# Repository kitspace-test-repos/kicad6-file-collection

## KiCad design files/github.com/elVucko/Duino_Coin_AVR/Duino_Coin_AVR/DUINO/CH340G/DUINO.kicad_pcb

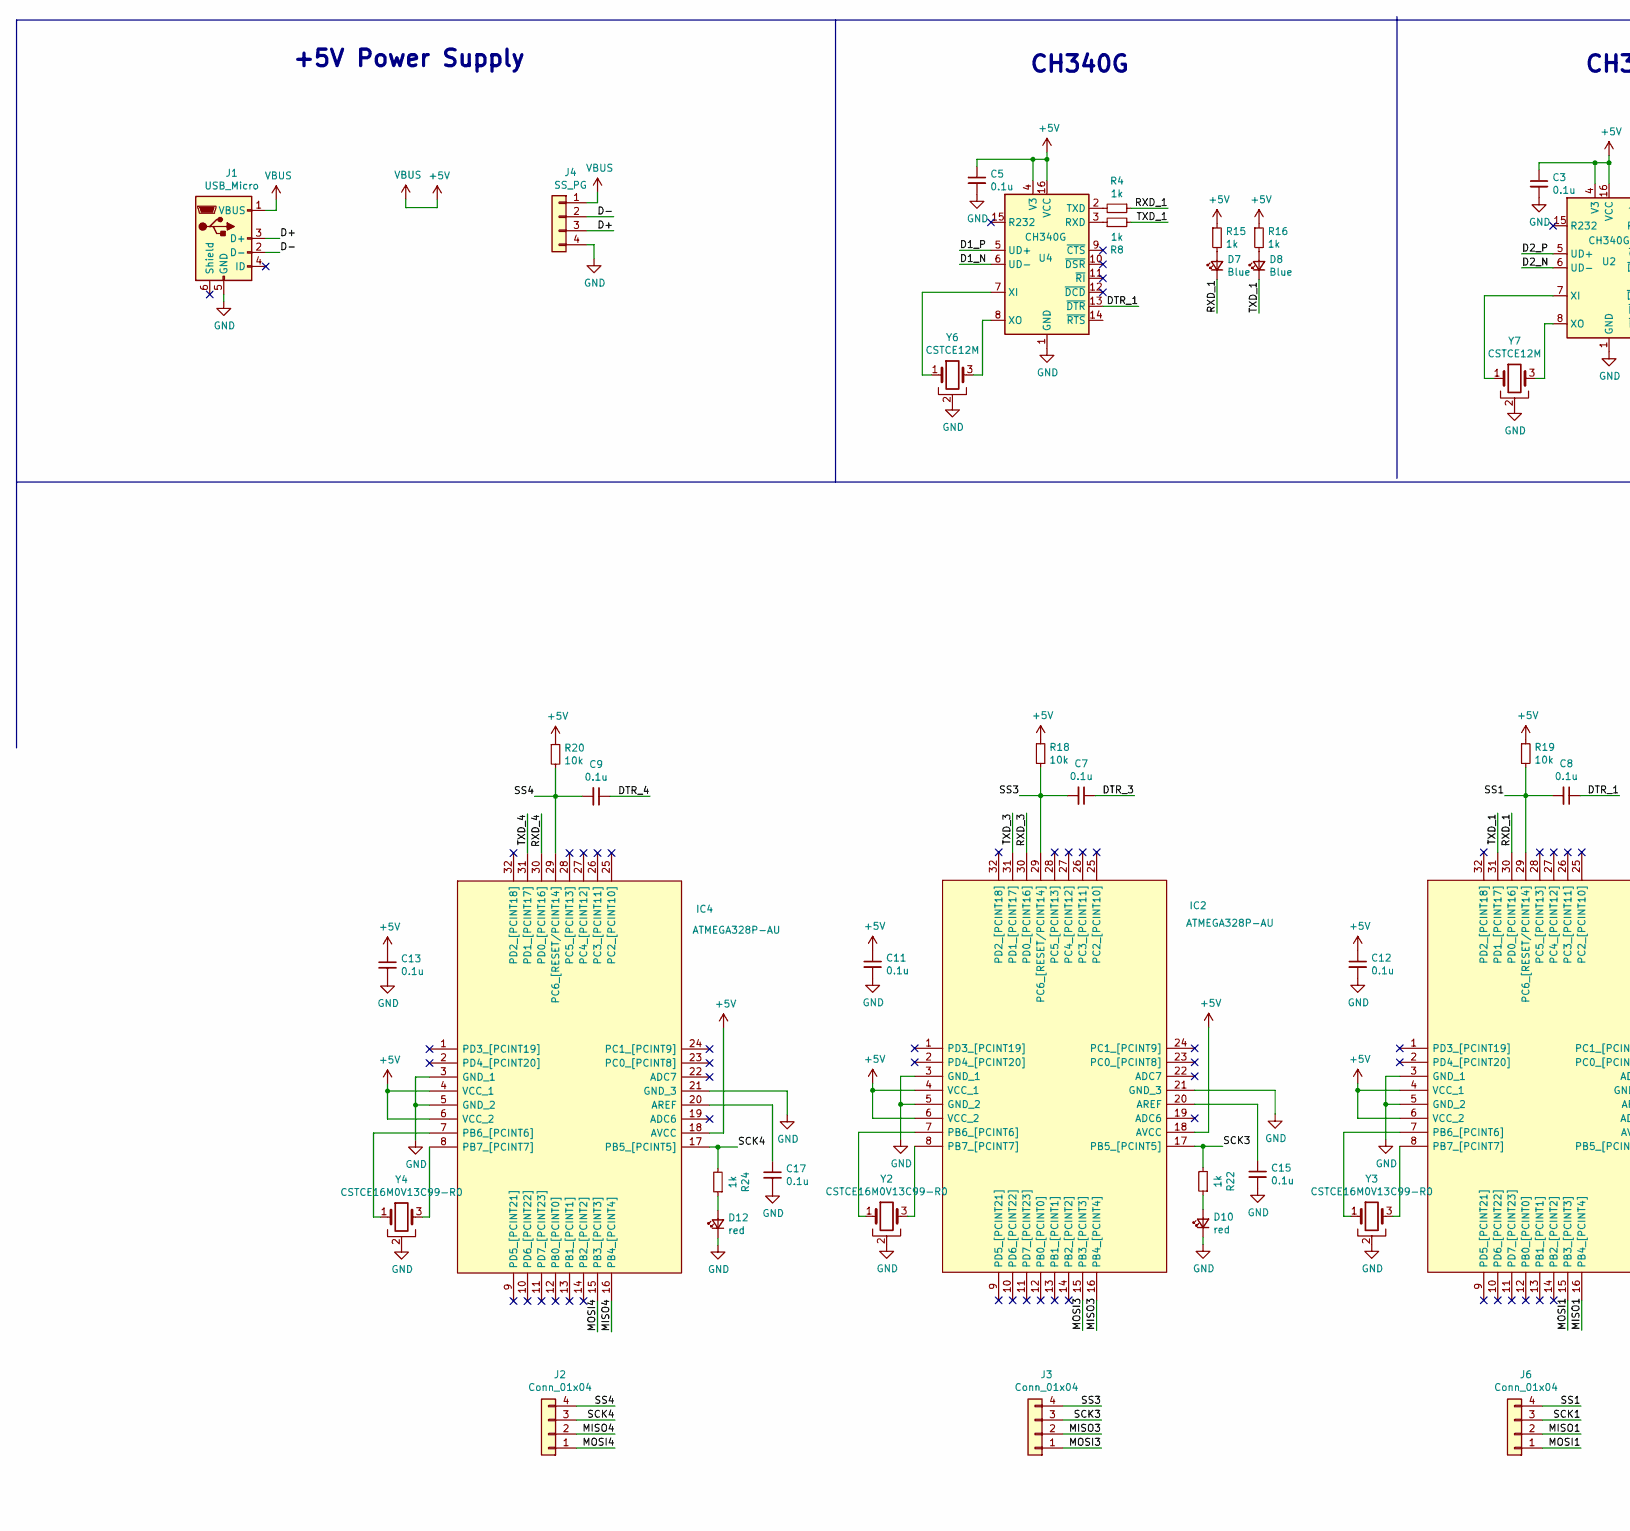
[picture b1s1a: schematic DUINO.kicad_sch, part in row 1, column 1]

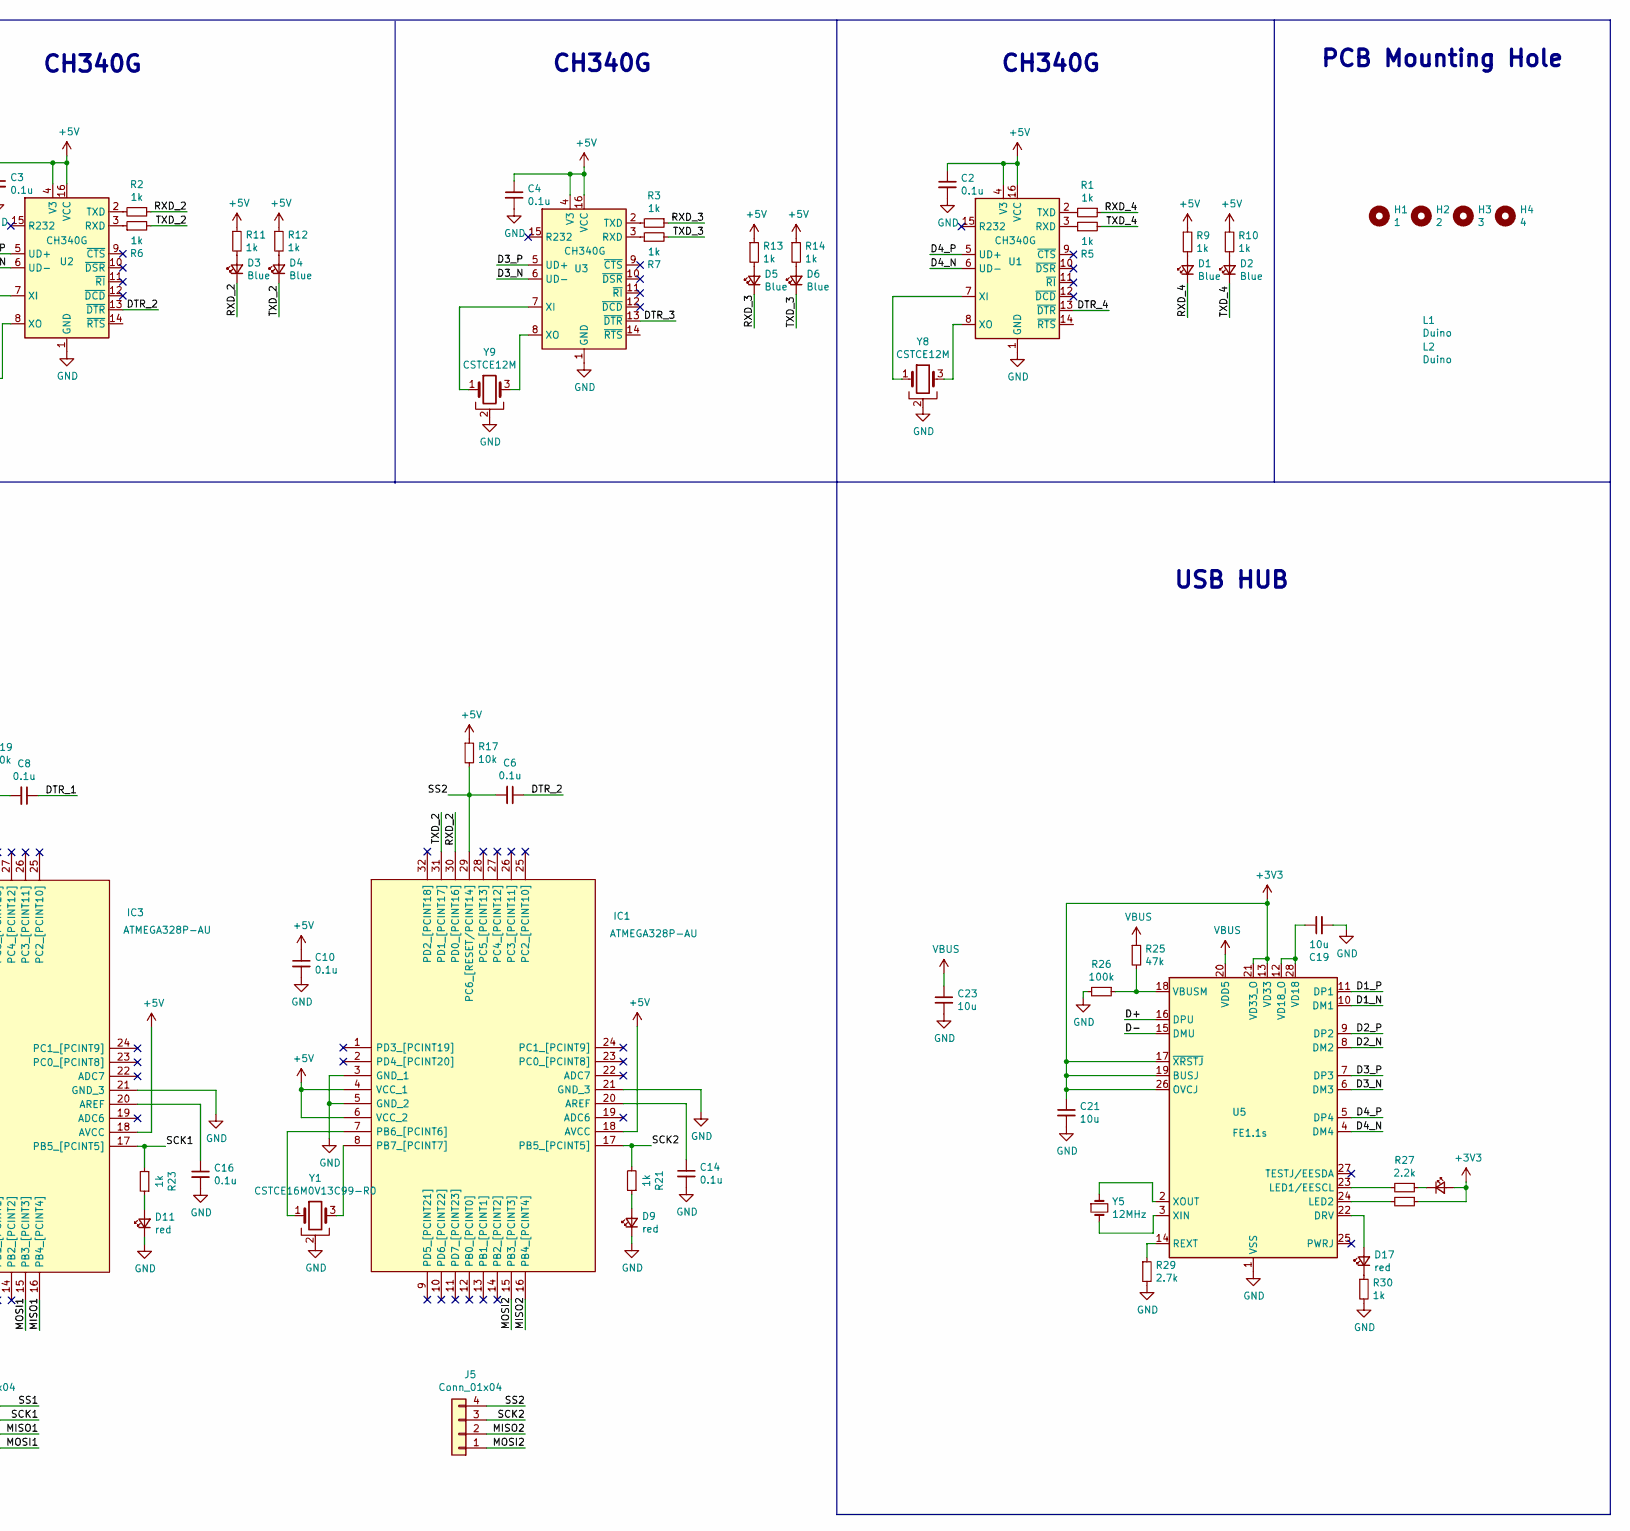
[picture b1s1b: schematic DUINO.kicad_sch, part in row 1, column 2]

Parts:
C2, C3, C4, C5, C6, C7, C8, C9, C10, C11, C12, C13, C14, C15, C16, C17: 0.1u; C_0805_2012Metric_Pad1.18x1.45mm_HandSolder
C19, C21, C23: 10u; C_0805_2012Metric_Pad1.18x1.45mm_HandSolder
D1, D2, D3, D4, D5, D6, D7, D8: Blue; LED_0603_1608Metric_Pad1.05x0.95mm_HandSolder
D9, D10, D11, D12, D17: red; LED_0603_1608Metric_Pad1.05x0.95mm_HandSolder
D13: 2; LED_0603_1608Metric_Pad1.05x0.95mm_HandSolder
H1: 1; MountingHole_3.2mm_M3
H2: 2; MountingHole_3.2mm_M3
H3: 3; MountingHole_3.2mm_M3
H4: 4; MountingHole_3.2mm_M3
IC1, IC2, IC3, IC4: ATMEGA328P-AU; QFP80P900X900X120-32N; Manufacturer_Part_Number ATMEGA328P-AU; Mouser Part Number 556-ATMEGA328P-AU
J1: USB_Micro; USB_Micro-B_Amphenol_10104110_Horizontal
J2, J3, J5, J6: Conn_01x04; PinHeader_1x04_P2.54mm_Vertical
J4: SS_PG; PinHeader_1x04_P2.54mm_Horizontal
L1, L2: Duino
R1, R2, R3, R4, R5, R6, R7, R8: 1k; R_0603_1608Metric_Pad0.98x0.95mm_HandSolder
R9, R10, R11, R12, R13, R14, R15, R16, R21, R22, R23, R24, R30: 1k; R_0805_2012Metric_Pad1.20x1.40mm_HandSolder
R17, R18, R19, R20: 10k; R_0805_2012Metric_Pad1.20x1.40mm_HandSolder
R25: 47k; R_0805_2012Metric_Pad1.20x1.40mm_HandSolder
R26: 100k; R_0805_2012Metric_Pad1.20x1.40mm_HandSolder
R27, R28: 2.2k; R_0805_2012Metric_Pad1.20x1.40mm_HandSolder
R29: 2.7k; R_0805_2012Metric_Pad1.20x1.40mm_HandSolder
U1, U2, U3, U4: CH340G; SOIC-16_3.9x9.9mm_P1.27mm
U5: FE1.1s; SSOP-28_3.9x9.9mm_P0.635mm
Y1, Y2, Y3, Y4: CSTCE16M0V13C99-R0; CSTCE16M0V13C99R0
Y5: 12MHz; Crystal_SMD_5032-2Pin_5.0x3.2mm
Y6, Y7, Y8, Y9: CSTCE12M; CSTCE16M0V13C99R0

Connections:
+3V3: C21.1, D13.2 (A), R28.1, U5.13 (VD33), U5.17 (~XRSTJ), U5.19 (BUSJ), U5.21 (VD33_O), U5.26 (OVCJ)
+5V: C2.1, C3.1, C4.1, C5.1, C10.1, C11.1, C12.1, C13.1, C23.1, IC1.4 (VCC_1), IC1.6 (VCC_2), IC1.18 (AVCC), IC2.4 (VCC_1), IC2.6 (VCC_2), IC2.18 (AVCC), IC3.4 (VCC_1), IC3.6 (VCC_2), IC3.18 (AVCC), IC4.4 (VCC_1), IC4.6 (VCC_2), IC4.18 (AVCC), J1.1 (VBUS), J4.1, R9.1, R10.1, R11.1, R12.1, R13.1, R14.1, R15.1, R16.1, R17.1, R18.1, R19.1, R20.1, R25.1, U1.4 (V3), U1.16 (VCC), U2.4 (V3), U2.16 (VCC), U3.4 (V3), U3.16 (VCC), U4.4 (V3), U4.16 (VCC), U5.20 (VDD5)
/D1_N: U4.6 (UD-), U5.10 (DM1)
/D1_P: U4.5 (UD+), U5.11 (DP1)
/D2_N: U2.6 (UD-), U5.8 (DM2)
/D2_P: U2.5 (UD+), U5.9 (DP2)
/D3_N: U3.6 (UD-), U5.6 (DM3)
/D3_P: U3.5 (UD+), U5.7 (DP3)
/D4_N: U1.6 (UD-), U5.4 (DM4)
/D4_P: U1.5 (UD+), U5.5 (DP4)
/D+: J1.3 (D+), J4.3, U5.16 (DPU)
/D-: J1.2 (D-), J4.2, U5.15 (DMU)
/DTR_1: C8.1, U4.13 (~DTR)
/DTR_2: C6.1, U2.13 (~DTR)
/DTR_3: C7.1, U3.13 (~DTR)
/DTR_4: C9.1, U1.13 (~DTR)
/MISO1: IC3.16 (PB4_[PCINT4]), J6.2
/MISO2: IC1.16 (PB4_[PCINT4]), J5.2
/MISO3: IC2.16 (PB4_[PCINT4]), J3.2
/MISO4: IC4.16 (PB4_[PCINT4]), J2.2
/MOSI1: IC3.15 (PB3_[PCINT3]), J6.1
/MOSI2: IC1.15 (PB3_[PCINT3]), J5.1
/MOSI3: IC2.15 (PB3_[PCINT3]), J3.1
/MOSI4: IC4.15 (PB3_[PCINT3]), J2.1
/RXD_1: D7.1 (K), IC3.30 (PD0_[PCINT16]), R4.1
/RXD_2: D3.1 (K), IC1.30 (PD0_[PCINT16]), R2.1
/RXD_3: D5.1 (K), IC2.30 (PD0_[PCINT16]), R3.1
/RXD_4: D1.1 (K), IC4.30 (PD0_[PCINT16]), R1.1
/SCK1: IC3.17 (PB5_[PCINT5]), J6.3, R23.2
/SCK2: IC1.17 (PB5_[PCINT5]), J5.3, R21.2
/SCK3: IC2.17 (PB5_[PCINT5]), J3.3, R22.2
/SCK4: IC4.17 (PB5_[PCINT5]), J2.3, R24.2
/SS1: C8.2, IC3.29 (PC6_[RESET/PCINT14]), J6.4, R19.2
/SS2: C6.2, IC1.29 (PC6_[RESET/PCINT14]), J5.4, R17.2
/SS3: C7.2, IC2.29 (PC6_[RESET/PCINT14]), J3.4, R18.2
/SS4: C9.2, IC4.29 (PC6_[RESET/PCINT14]), J2.4, R20.2
/TXD_1: D8.1 (K), IC3.31 (PD1_[PCINT17]), R8.2
/TXD_2: D4.1 (K), IC1.31 (PD1_[PCINT17]), R6.2
/TXD_3: D6.1 (K), IC2.31 (PD1_[PCINT17]), R7.2
/TXD_4: D2.1 (K), IC4.31 (PD1_[PCINT17]), R5.2
GND: C2.2, C3.2, C4.2, C5.2, C10.2, C11.2, C12.2, C13.2, C14.2, C15.2, C16.2, C17.2, C19.2, C21.2, C23.2, D9.1 (K), D10.1 (K), D11.1 (K), D12.1 (K), IC1.3 (GND_1), IC1.5 (GND_2), IC1.21 (GND_3), IC2.3 (GND_1), IC2.5 (GND_2), IC2.21 (GND_3), IC3.3 (GND_1), IC3.5 (GND_2), IC3.21 (GND_3), IC4.3 (GND_1), IC4.5 (GND_2), IC4.21 (GND_3), J1.5 (GND), J4.4, R26.2, R29.2, R30.2, U1.1 (GND), U2.1 (GND), U3.1 (GND), U4.1 (GND), U5.1 (VSS), Y1.2, Y2.2, Y3.2, Y4.2, Y6.2, Y7.2, Y8.2, Y9.2
unnamed: C14.1, IC1.20 (AREF)
unnamed: C15.1, IC2.20 (AREF)
unnamed: C16.1, IC3.20 (AREF)
unnamed: C17.1, IC4.20 (AREF)
unnamed: C19.1, U5.12 (VD18_O), U5.28 (VD18)
unnamed: D1.2 (A), R9.2
unnamed: D2.2 (A), R10.2
unnamed: D3.2 (A), R11.2
unnamed: D4.2 (A), R12.2
unnamed: D5.2 (A), R13.2
unnamed: D6.2 (A), R14.2
unnamed: D7.2 (A), R15.2
unnamed: D8.2 (A), R16.2
unnamed: D9.2 (A), R21.1
unnamed: D10.2 (A), R22.1
unnamed: D11.2 (A), R23.1
unnamed: D12.2 (A), R24.1
unnamed: D13.1 (K), R27.1
unnamed: D17.1 (K), R30.1
unnamed: D17.2 (A), U5.22 (DRV)
unnamed: IC1.7 (PB6_[PCINT6]), Y1.1
unnamed: IC1.8 (PB7_[PCINT7]), Y1.3
unnamed: IC2.7 (PB6_[PCINT6]), Y2.1
unnamed: IC2.8 (PB7_[PCINT7]), Y2.3
unnamed: IC3.7 (PB6_[PCINT6]), Y3.1
unnamed: IC3.8 (PB7_[PCINT7]), Y3.3
unnamed: IC4.7 (PB6_[PCINT6]), Y4.1
unnamed: IC4.8 (PB7_[PCINT7]), Y4.3
unnamed: R1.2, U1.2 (TXD)
unnamed: R2.2, U2.2 (TXD)
unnamed: R3.2, U3.2 (TXD)
unnamed: R4.2, U4.2 (TXD)
unnamed: R5.1, U1.3 (RXD)
unnamed: R6.1, U2.3 (RXD)
unnamed: R7.1, U3.3 (RXD)
unnamed: R8.1, U4.3 (RXD)
unnamed: R25.2, R26.1, U5.18 (VBUSM)
unnamed: R27.2, U5.23 (LED1/EESCL)
unnamed: R28.2, U5.24 (LED2)
unnamed: R29.1, U5.14 (REXT)
unnamed: U1.7 (XI), Y8.1
unnamed: U1.8 (XO), Y8.3
unnamed: U2.7 (XI), Y7.1
unnamed: U2.8 (XO), Y7.3
unnamed: U3.7 (XI), Y9.1
unnamed: U3.8 (XO), Y9.3
unnamed: U4.7 (XI), Y6.1
unnamed: U4.8 (XO), Y6.3
unnamed: U5.2 (XOUT), Y5.1
unnamed: U5.3 (XIN), Y5.2

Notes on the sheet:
CH340G
USB HUB
+5V Power Supply
PCB Mounting Hole

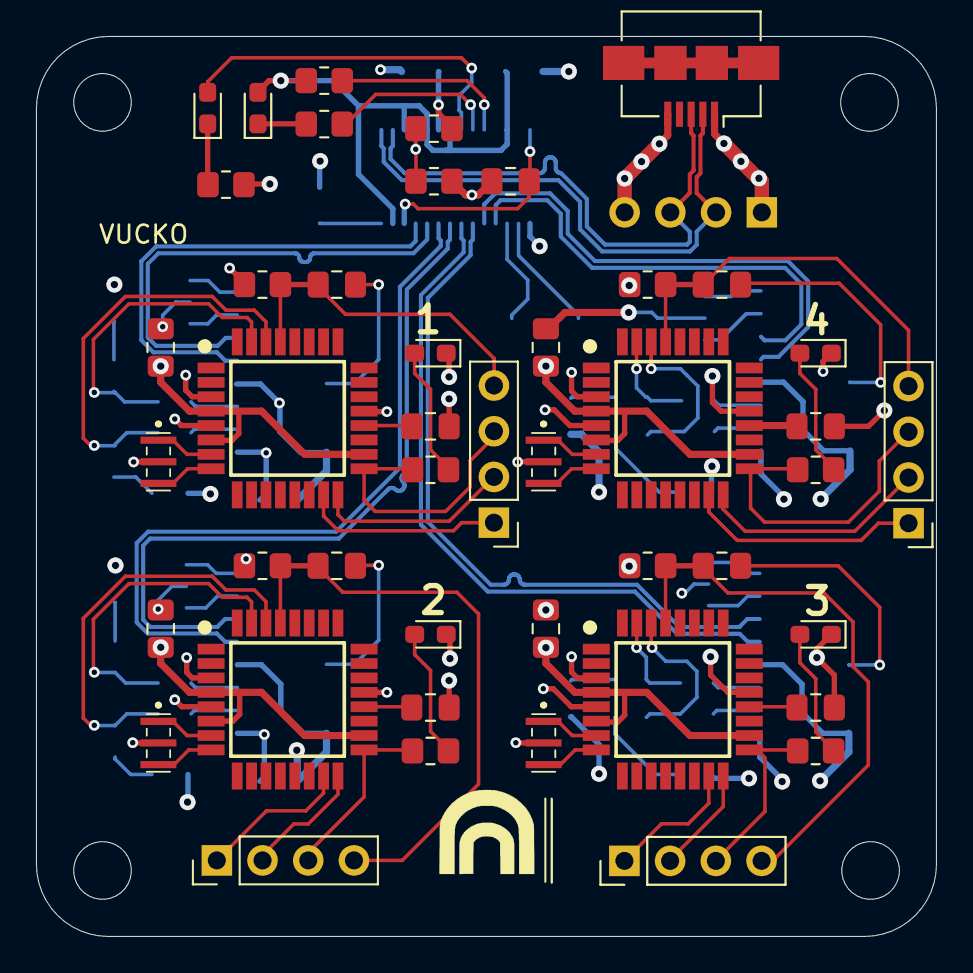
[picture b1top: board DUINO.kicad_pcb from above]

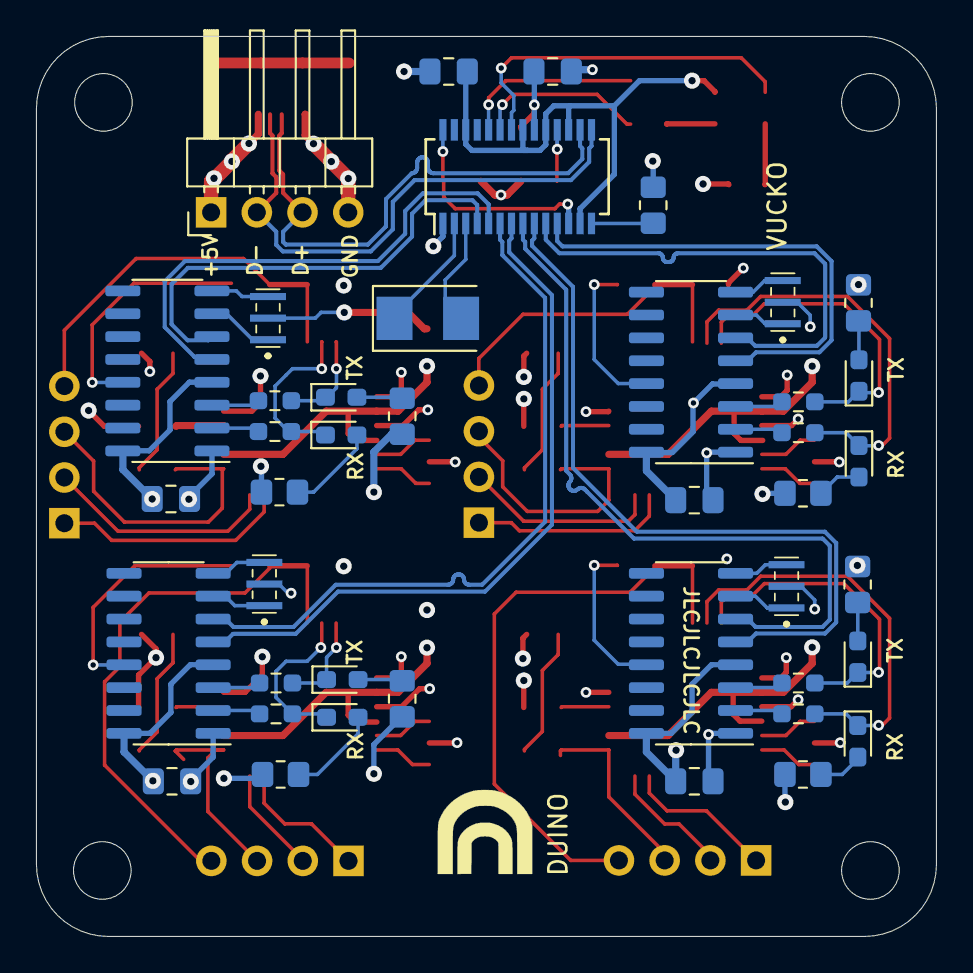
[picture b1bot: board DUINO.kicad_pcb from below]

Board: 4 copper layers, 50.0 x 50.0 mm, 93 parts (43 on the bottom side), 91 nets.

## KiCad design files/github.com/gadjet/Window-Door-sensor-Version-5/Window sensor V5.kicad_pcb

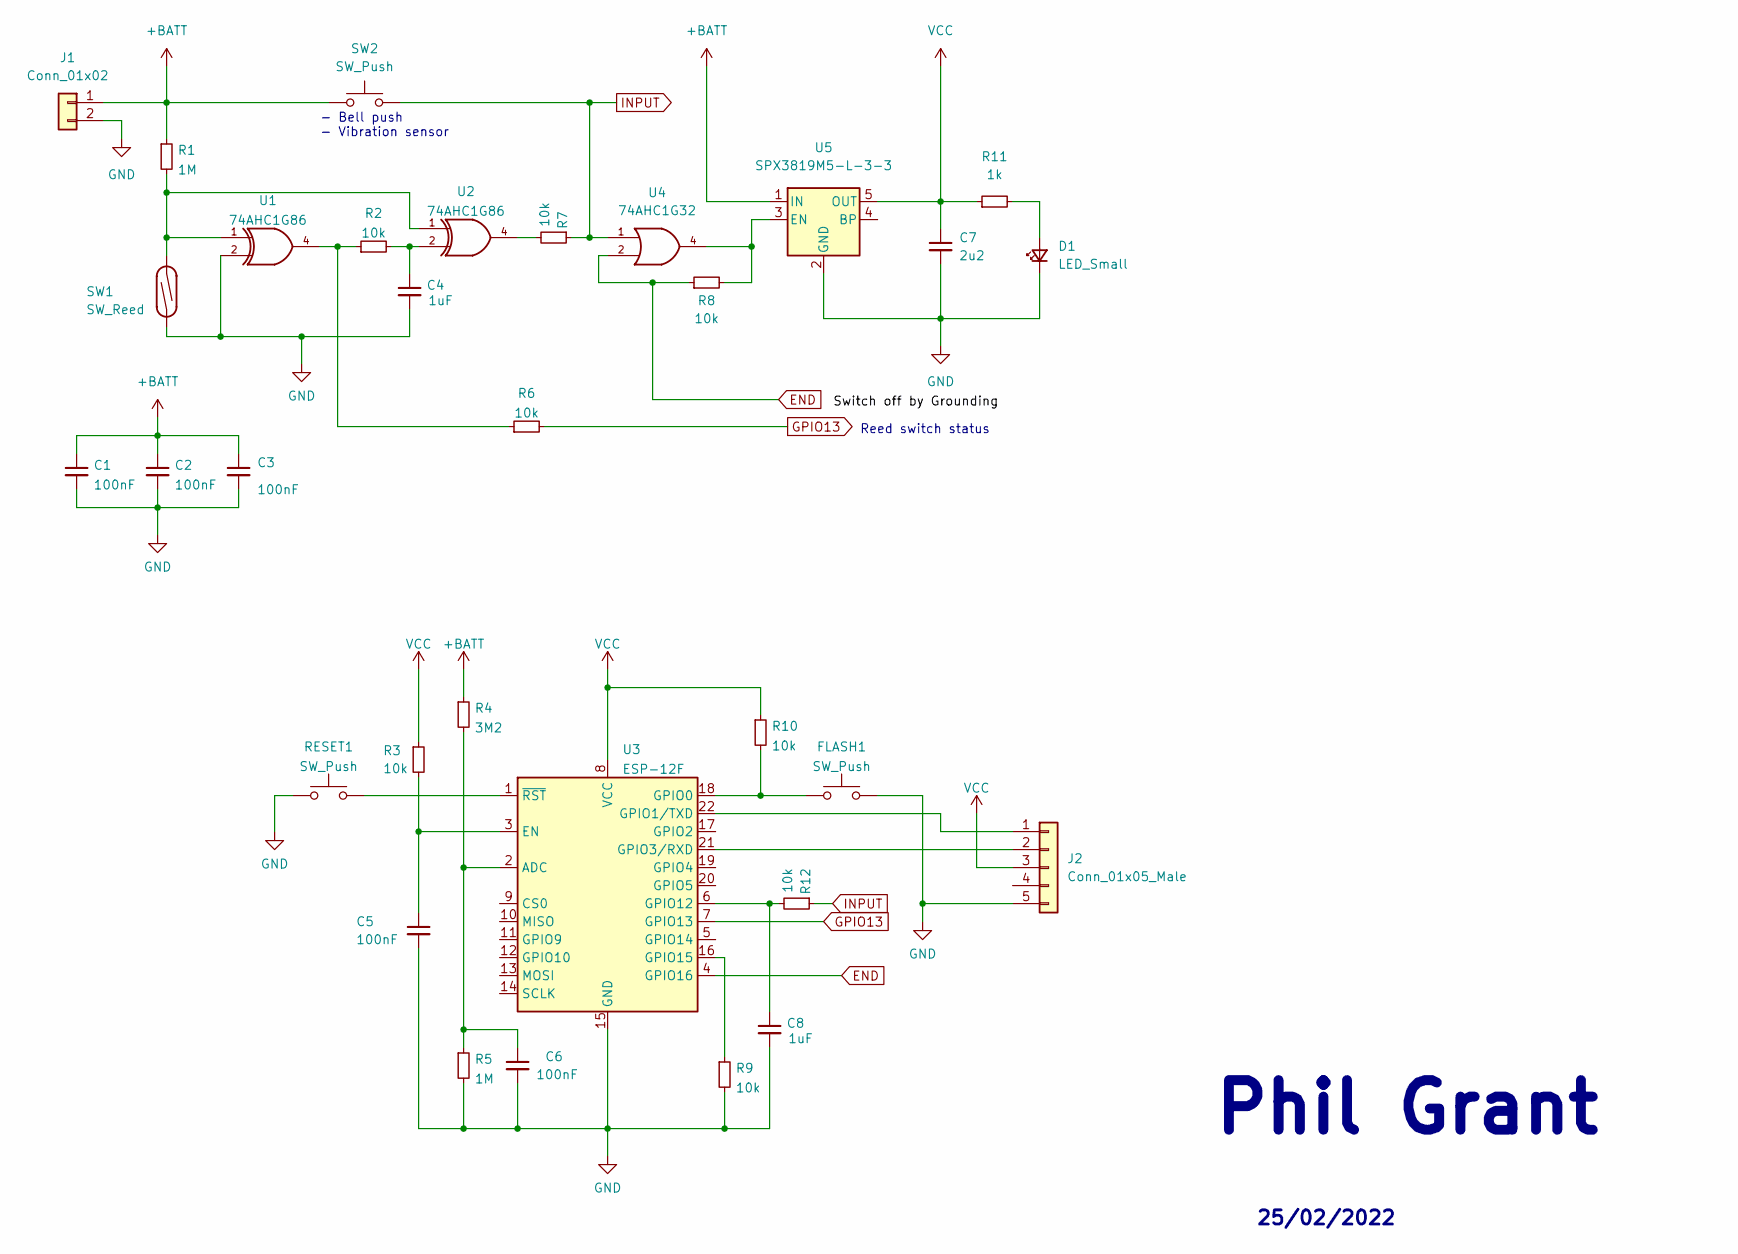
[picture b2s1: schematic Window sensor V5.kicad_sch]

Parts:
C1, C2, C3, C5, C6: 100nF; C_0603_1608Metric
C4, C8: 1uF; C_0603_1608Metric
C7: 2u2; C_0603_1608Metric
D1: LED_Small; LED_0805_2012Metric
FLASH1: SW_Push; SW_Push_SPST_NO_Alps_SKRK
J1: Conn_01x02; JST_PH_S2B-PH-K_1x02_P2.00mm_Horizontal
J2: Conn_01x05_Male; PinHeader_1x05_P2.54mm_Vertical
R1, R5: 1M; R_0603_1608Metric
R2, R3, R6, R7, R8, R9, R10, R12: 10k; R_0603_1608Metric
R4: 3M2; R_0603_1608Metric
R11: 1k; R_0603_1608Metric
RESET1: SW_Push; SW_Push_SPST_NO_Alps_SKRK
SW1: SW_Reed; SW_SPST_REED_CT10-XXXX-G2
SW2: SW_Push; SW_PUSH_6mm_H4.3mm
U1, U2: 74AHC1G86; SOT-23-5
U3: ESP-12F; ESP-12E
U4: 74AHC1G32; SOT-23-5
U5: SPX3819M5-L-3-3; SOT-23-5

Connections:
+BATT: C1.1, C2.1, C3.1, J1.1, R1.1, R4.1, SW2.1, U1.5 (+BATT), U2.5 (+BATT), U4.5 (+BATT), U5.1 (IN)
END: R8.1, U3.4 (GPIO16), U4.2
GND: C1.2, C2.2, C3.2, C4.2, C5.2, C6.2, C7.2, C8.2, D1.1 (K), FLASH1.2, J1.2, J2.5, R5.2, R9.2, RESET1.1, SW1.1, U1.2, U1.3 (GND), U2.3 (GND), U3.15 (GND), U4.3 (GND), U5.2 (GND); also elsewhere on the board
GPIO13: R6.2, U3.7 (GPIO13)
INPUT: R7.1, R12.1, SW2.2, U4.1
unnamed: C4.1, R2.2, U2.2
unnamed: C5.1, R3.2, U3.3 (EN)
unnamed: C6.1, R4.2, R5.1, U3.2 (ADC)
unnamed: C8.1, R12.2, U3.6 (GPIO12)
unnamed: D1.2 (A), R11.2
unnamed 10: FLASH1.1, R10.2, U3.18 (GPIO0); also elsewhere on the board
unnamed: J2.1, U3.22 (GPIO1/TXD)
unnamed: J2.2, U3.21 (GPIO3/RXD)
unnamed: R1.2, SW1.2, U1.1, U2.1
unnamed: R2.1, R6.1, U1.4
unnamed: R7.2, U2.4
unnamed: R8.2, U4.4, U5.3 (EN)
unnamed: R9.1, U3.16 (GPIO15)
unnamed 18: RESET1.2, U3.1 (~RST); also elsewhere on the board
VCC: C7.1, J2.3, R3.1, R10.1, R11.1, U3.8 (VCC), U5.5 (OUT)

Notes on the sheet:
- Bell push - Vibration sensor
25/02/2022
Reed switch status
Phil Grant

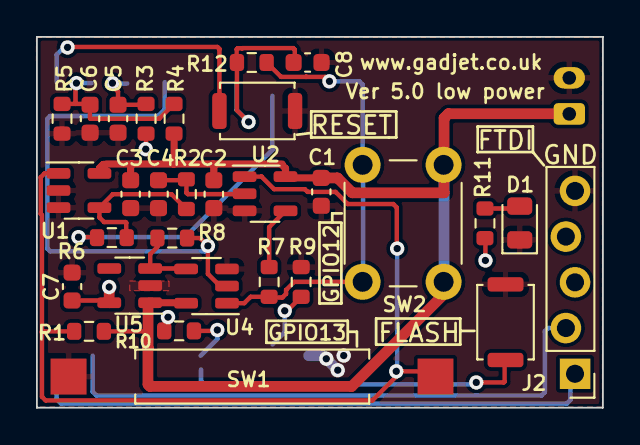
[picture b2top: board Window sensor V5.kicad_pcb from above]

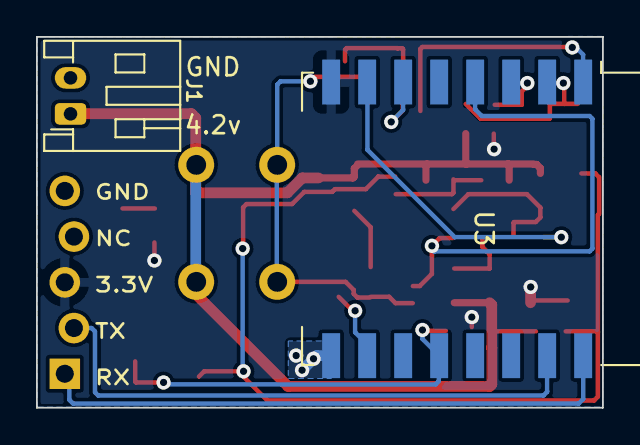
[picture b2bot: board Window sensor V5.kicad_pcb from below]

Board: 2 copper layers, 31.4 x 20.6 mm, 32 parts (2 on the bottom side), 20 nets.

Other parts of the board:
FLASH: SW_Push; SW_Push_SPST_NO_Alps_SKRK
RESET: SW_Push; SW_Push_SPST_NO_Alps_SKRK

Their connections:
GND: FLASH.2, RESET.1; also elsewhere on the board
unnamed 10: FLASH.1; also elsewhere on the board
unnamed 18: RESET.2; also elsewhere on the board

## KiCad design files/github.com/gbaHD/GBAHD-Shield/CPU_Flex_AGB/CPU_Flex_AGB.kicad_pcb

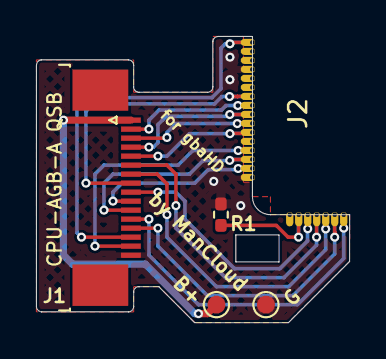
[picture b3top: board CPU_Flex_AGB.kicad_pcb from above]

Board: 2 copper layers, 17.4 x 15.9 mm, 5 parts (0 on the bottom side), 17 nets.

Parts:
B+: BAT+; TestPoint_Pad_D1.0mm
G: GND; TestPoint_Pad_D1.0mm
J1: Conn_01x16; TE_1-1734839-6_1x16-1MP_P0.5mm_Horizontal
J2: CPU_AGB_A_Interface; CPU_AGB_A_INTERFACE
R1: 100k; R_0402_1005Metric_Pad0.72x0.64mm_HandSolder

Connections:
GND: G.1, J1.16, J2.116 (GND), J2.128 (GND), R1.1
unnamed: J1.2, J2.120 (TP6)
unnamed: J1.3, J2.122 (TP7)
unnamed: J1.4, J2.121 (TP5)
unnamed: J1.5, J2.123 (TP4)
unnamed: J1.6, J2.4 (TP0)
unnamed: J1.7, J2.5 (TP1)
unnamed: J1.8, J2.119 (TP9)
unnamed: J1.9, J2.3 (TP8)
unnamed: J1.10, J2.127 (TP3)
unnamed: J1.11, J2.126 (TP2)
unnamed: J1.12, J2.7 (S02)
unnamed: J1.13, J2.6 (S01)
unnamed: J1.14, J2.113 (CK1)
unnamed: J1.15, J2.125 (RESET)
unnamed: J2.2 (IN35), R1.2
VCC: B+.1, J1.1

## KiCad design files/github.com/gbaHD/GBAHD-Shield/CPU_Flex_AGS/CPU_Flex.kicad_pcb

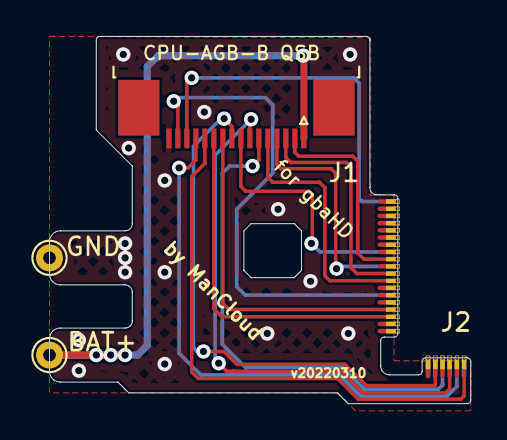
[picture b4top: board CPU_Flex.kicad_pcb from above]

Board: 2 copper layers, 23.4 x 20.4 mm, 4 parts (0 on the bottom side), 16 nets.

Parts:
BAT+: Conn_01x01; TestPoint_THTPad_D1.5mm_Drill0.7mm
GND: Conn_01x01; TestPoint_THTPad_D1.5mm_Drill0.7mm
J1: Conn_01x16; TE_1-1734839-6_1x16-1MP_P0.5mm_Horizontal
J2: CPU AGB B Interface; CPU_AGB_B_Interface

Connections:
/GBA_A: J1.6, J2.3 (TP0)
/GBA_AUD_L: J1.12, J2.6 (S02)
/GBA_AUD_R: J1.13, J2.5 (S01)
/GBA_B: J1.7, J2.4 (TP1)
/GBA_CLK: J1.14, J2.138 (CK1)
/GBA_DOWN: J1.3, J2.148 (TP7)
/GBA_L: J1.8, J2.145 (TP9)
/GBA_LEFT: J1.4, J2.147 (TP5)
/GBA_R: J1.9, J2.2 (TP8)
/GBA_RESET: J1.15, J2.151 (RESET)
/GBA_RIGHT: J1.5, J2.149 (TP4)
/GBA_SELECT: J1.11, J2.154 (TP2)
/GBA_START: J1.10, J2.153 (TP3)
/GBA_UP: J1.2, J2.146 (TP6)
GND: GND.1, J1.16
VCC: BAT+.1, J1.1

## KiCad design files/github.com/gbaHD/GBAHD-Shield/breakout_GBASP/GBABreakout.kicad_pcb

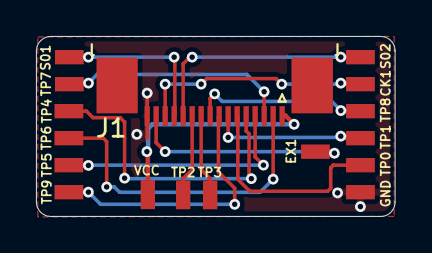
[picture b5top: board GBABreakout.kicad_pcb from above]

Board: 2 copper layers, 19.9 x 10.0 mm, 17 parts (0 on the bottom side), 16 nets.

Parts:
J1: Conn_01x16; TE_1-1734839-6_1x16-1MP_P0.5mm_Horizontal
J2: VCC; SOLDER_PAD
J3: TP6; SOLDER_PAD
J4: TP7; SOLDER_PAD
J5: TP5; SOLDER_PAD
J6: TP4; SOLDER_PAD
J7: TP0; SOLDER_PAD
J8: TP1; SOLDER_PAD
J9: TP9; SOLDER_PAD
J10: TP8; SOLDER_PAD
J11: TP3; SOLDER_PAD
J12: TP2; SOLDER_PAD
J13: S02; SOLDER_PAD
J14: S01; SOLDER_PAD
J15: CK1; SOLDER_PAD
J16: EX1; SOLDER_PAD
J17: GND; SOLDER_PAD

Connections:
EX1: J1.15, J16.1
GBA_A: J1.6, J7.1
GBA_AUD1: J1.13, J14.1
GBA_AUD2: J1.12, J13.1
GBA_B: J1.7, J8.1
GBA_CLK: J1.14, J15.1
GBA_DOWN: J1.3, J4.1
GBA_L: J1.8, J9.1
GBA_LEFT: J1.4, J5.1
GBA_R: J1.9, J10.1
GBA_RIGHT: J1.5, J6.1
GBA_SELECT: J1.11, J12.1
GBA_START: J1.10, J11.1
GBA_UP: J1.2, J3.1
GBA_VCC: J1.1, J2.1
GND: J1.16, J17.1

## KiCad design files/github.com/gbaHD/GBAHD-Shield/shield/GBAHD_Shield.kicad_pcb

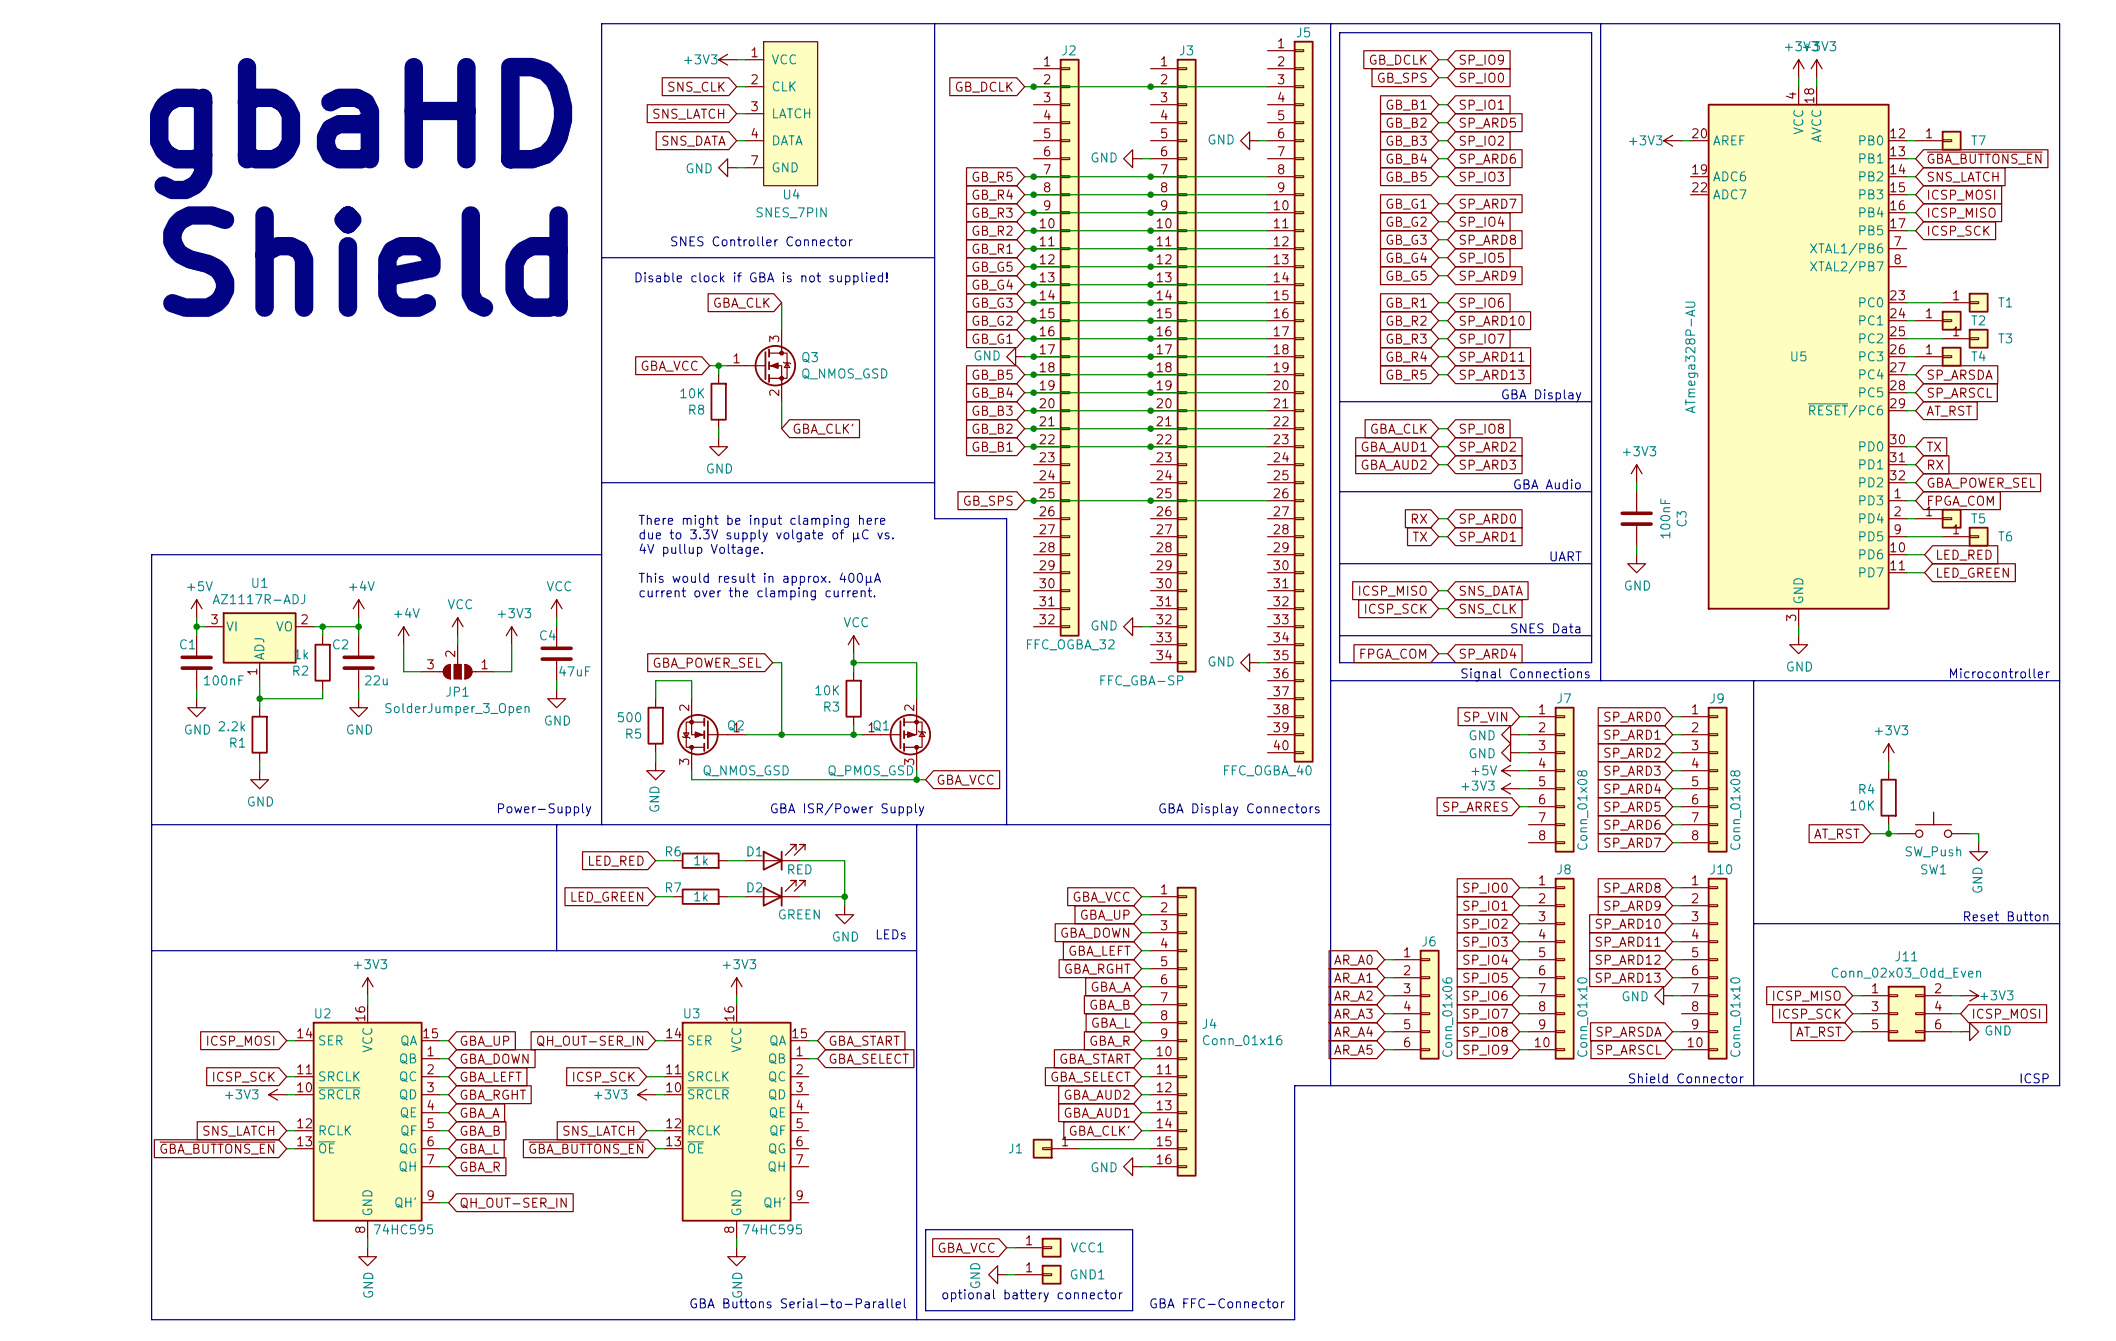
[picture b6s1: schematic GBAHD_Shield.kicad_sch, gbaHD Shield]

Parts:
C1, C3: 100nF; C_0805_2012Metric_Pad1.18x1.45mm_HandSolder
C2: 22u; C_0805_2012Metric_Pad1.18x1.45mm_HandSolder
C4: 47uF; C_0805_2012Metric_Pad1.18x1.45mm_HandSolder
D1: RED; LED_0805_2012Metric_Pad1.15x1.40mm_HandSolder
D2: GREEN; LED_0805_2012Metric_Pad1.15x1.40mm_HandSolder
GND1: Conn_01x01; TestPoint_Pad_1.5x1.5mm
J1: Conn_01x01; TestPoint_Pad_1.5x1.5mm
J2: FFC_OGBA_32; TE_3-1734839-2_1x32-1MP_P0.5mm_Horizontal
J3: FFC_GBA-SP; TE_3-1734839-4_1x34-1MP_P0.5mm_Horizontal
J4: Conn_01x16; TE_1-1734839-6_1x16-1MP_P0.5mm_Horizontal
J5: FFC_OGBA_40; TE_4-1734839-0_1x40-1MP_P0.5mm_Horizontal
J6: Conn_01x06; PinHeader_1x06_P2.54mm_Vertical
J7, J9: Conn_01x08; PinHeader_1x08_P2.54mm_Vertical
J8, J10: Conn_01x10; PinHeader_1x10_P2.54mm_Vertical
J11: Conn_02x03_Odd_Even; PinHeader_2x03_P2.54mm_Vertical
JP1: SolderJumper_3_Open; SolderJumper-3_P1.3mm_Open_Pad1.0x1.5mm_NumberLabels
Q1: Q_PMOS_GSD; SOT-23
Q2, Q3: Q_NMOS_GSD; SOT-23
R1: 2.2k; R_0805_2012Metric_Pad1.20x1.40mm_HandSolder
R2, R6, R7: 1k; R_0805_2012Metric_Pad1.20x1.40mm_HandSolder
R3, R4, R8: 10K; R_0805_2012Metric_Pad1.20x1.40mm_HandSolder
R5: 500; R_0805_2012Metric_Pad1.20x1.40mm_HandSolder
SW1: SW_Push; SW_Push_1P1T_NO_CK_KMR2
T1, T2, T3, T4, T5, T6, T7: Conn_01x01; TestPoint_Pad_D1.5mm
U1: AZ1117R-ADJ; SOT-89-3
U2, U3: 74HC595; SOIC-16_3.9x9.9mm_P1.27mm
U4: SNES_7PIN
U5: ATmega328P-AU; TQFP-32_7x7mm_P0.8mm
VCC1: Conn_01x01; TestPoint_Pad_1.5x1.5mm

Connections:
+3V3: C3.2, J7.5, J11.2, JP1.1 (A), R4.1, U2.10 (~SRCLR), U2.16 (VCC), U3.10 (~SRCLR), U3.16 (VCC), U4.1 (VCC), U5.4 (VCC), U5.6 (VCC), U5.18 (AVCC), U5.20 (AREF)
+4V: C2.2, JP1.3 (B), R2.2, U1.2 (VO)
+5V: C1.2, J7.4, U1.3 (VI)
AR_A0: J6.1
AR_A1: J6.2
AR_A2: J6.3
AR_A3: J6.4
AR_A4: J6.5
AR_A5: J6.6
AT_RST: J11.5, R4.2, SW1.1, U5.29 (~RESET/PC6)
FPGA_COM: J9.5, U5.1 (PD3)
GBA_A: J4.6, U2.4 (QE)
GBA_AUD1: J4.13, J9.3
GBA_AUD2: J4.12, J9.4
GBA_B: J4.7, U2.5 (QF)
GBA_CLK: J8.9, Q3.3 (D)
GBA_CLK': J4.14, Q3.2 (S)
GBA_DOWN: J4.3, U2.1 (QB)
GBA_L: J4.8, U2.6 (QG)
GBA_LEFT: J4.4, U2.2 (QC)
GBA_POWER_SEL: Q1.1 (G), Q2.1 (G), R3.1, U5.32 (PD2)
GBA_R: J4.9, U2.7 (QH)
GBA_RGHT: J4.5, U2.3 (QD)
GBA_SELECT: J4.11, U3.1 (QB)
GBA_START: J4.10, U3.15 (QA)
GBA_UP: J4.2, U2.15 (QA)
GBA_VCC: J4.1, Q1.3 (D), Q2.3 (D), Q3.1 (G), R8.2, VCC1.1
GB_B1: J2.22, J3.22, J5.23, J8.2
GB_B2: J2.21, J3.21, J5.22, J9.6
GB_B3: J2.20, J3.20, J5.21, J8.3
GB_B4: J2.19, J3.19, J5.20, J9.7
GB_B5: J2.18, J3.18, J5.19, J8.4
GB_DCLK: J2.2, J3.2, J5.3, J8.10
GB_G1: J2.16, J3.16, J5.17, J9.8
GB_G2: J2.15, J3.15, J5.16, J8.5
GB_G3: J2.14, J3.14, J5.15, J10.1
GB_G4: J2.13, J3.13, J5.14, J8.6
GB_G5: J2.12, J3.12, J5.13, J10.2
GB_R1: J2.11, J3.11, J5.12, J8.7
GB_R2: J2.10, J3.10, J5.11, J10.3
GB_R3: J2.9, J3.9, J5.10, J8.8
GB_R4: J2.8, J3.8, J5.9, J10.4
GB_R5: J2.7, J3.7, J5.8, J10.6
GB_SPS: J2.25, J3.25, J5.26, J8.1
GND: C1.1, C2.1, C3.1, C4.1, D1.1 (K), D2.1 (K), GND1.1, J2.17, J3.6, J3.17, J3.32, J4.16, J5.6, J5.18, J5.35, J7.2, J7.3, J10.7, J11.6, R1.1, R5.1, R8.1, SW1.2, U2.8 (GND), U3.8 (GND), U4.7 (GND), U5.3 (GND), U5.5 (GND), U5.21 (GND)
ICSP_MISO: J11.1, U4.4 (DATA), U5.16 (PB4)
ICSP_MOSI: J11.4, U2.14 (SER), U5.15 (PB3)
ICSP_SCK: J11.3, U2.11 (SRCLK), U3.11 (SRCLK), U4.2 (CLK), U5.17 (PB5)
LED_GREEN: R7.1, U5.11 (PD7)
LED_RED: R6.1, U5.10 (PD6)
unnamed: D1.2 (A), R6.2
unnamed: D2.2 (A), R7.2
unnamed: J1.1, J4.15
unnamed: Q2.2 (S), R5.2
unnamed: R1.2, R2.1, U1.1 (ADJ)
unnamed: T1.1, U5.23 (PC0)
unnamed: T2.1, U5.24 (PC1)
unnamed: T3.1, U5.25 (PC2)
unnamed: T4.1, U5.26 (PC3)
unnamed: T5.1, U5.2 (PD4)
unnamed: T6.1, U5.9 (PD5)
unnamed: T7.1, U5.12 (PB0)
QH_OUT-SER_IN: U2.9 (QH'), U3.14 (SER)
RX: J9.1, U5.31 (PD1)
SNS_LATCH: U2.12 (RCLK), U3.12 (RCLK), U4.3 (LATCH), U5.14 (PB2)
SP_ARD1: J9.2, U5.30 (PD0)
SP_ARD12: J10.5
SP_ARRES: J7.6
SP_ARSCL: J10.10, U5.28 (PC5)
SP_ARSDA: J10.9, U5.27 (PC4)
SP_VIN: J7.1
VCC: C4.2, JP1.2 (C), Q1.2 (S), R3.2
~GBA_BUTTONS_EN: U2.13 (~OE), U3.13 (~OE), U5.13 (PB1)

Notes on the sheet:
ICSP
GBA Buttons Serial-to-Parallel
GBA FFC-Connector
GBA ISR/Power Supply
SNES Data
optional battery connector
There might be input clamping here due to 3.3V supply volgate of µC vs. 4V pullup Voltage. This would result in approx. 400µA current over the clamping current.
Microcontroller
GBA Display Connectors
Shield Connector
gbaHD Shield
UART
LEDs
Power-Supply
Disable clock if GBA is not supplied!
SNES Controller Connector
Reset Button
Signal Connections
GBA Display
GBA Audio

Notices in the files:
files/github.com/ghent360/PrntrBoardV2/hardware/WiFi-Addon.kicad_pcb:
(C) 2021 by Hijax_PL
